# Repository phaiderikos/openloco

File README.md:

> An open source and open hardware DCC decoder for locomotives.

Details.

## Getting started

A quick introduction to get it working.

### PCB

Required PCB capabilities for manifacturing.

### BOM

Table.

### Assembling

Some notes on component placement and soldering.

### Programming

Other notes on SWD.

### Wiring

Table and explanation.

## Features

* Tiny
* Open Hardware and Open Source
* Fully programmable and customizable
* other

## Configuration

Here you should write what are all of the configurations a user can enter when
using the project.

## Contributing

If you'd like to contribute, please fork the repository and use a feature
branch. Pull requests are warmly welcome.

## Links

- Project homepage: none
- Repository: https://github.com/federico1564S/openloco
- Issue tracker: https://github.com/federico1564S/openloco/issues
- Related projects:
  - 1
  - 2

## Licensing

This project is licensed under GPL3 license.

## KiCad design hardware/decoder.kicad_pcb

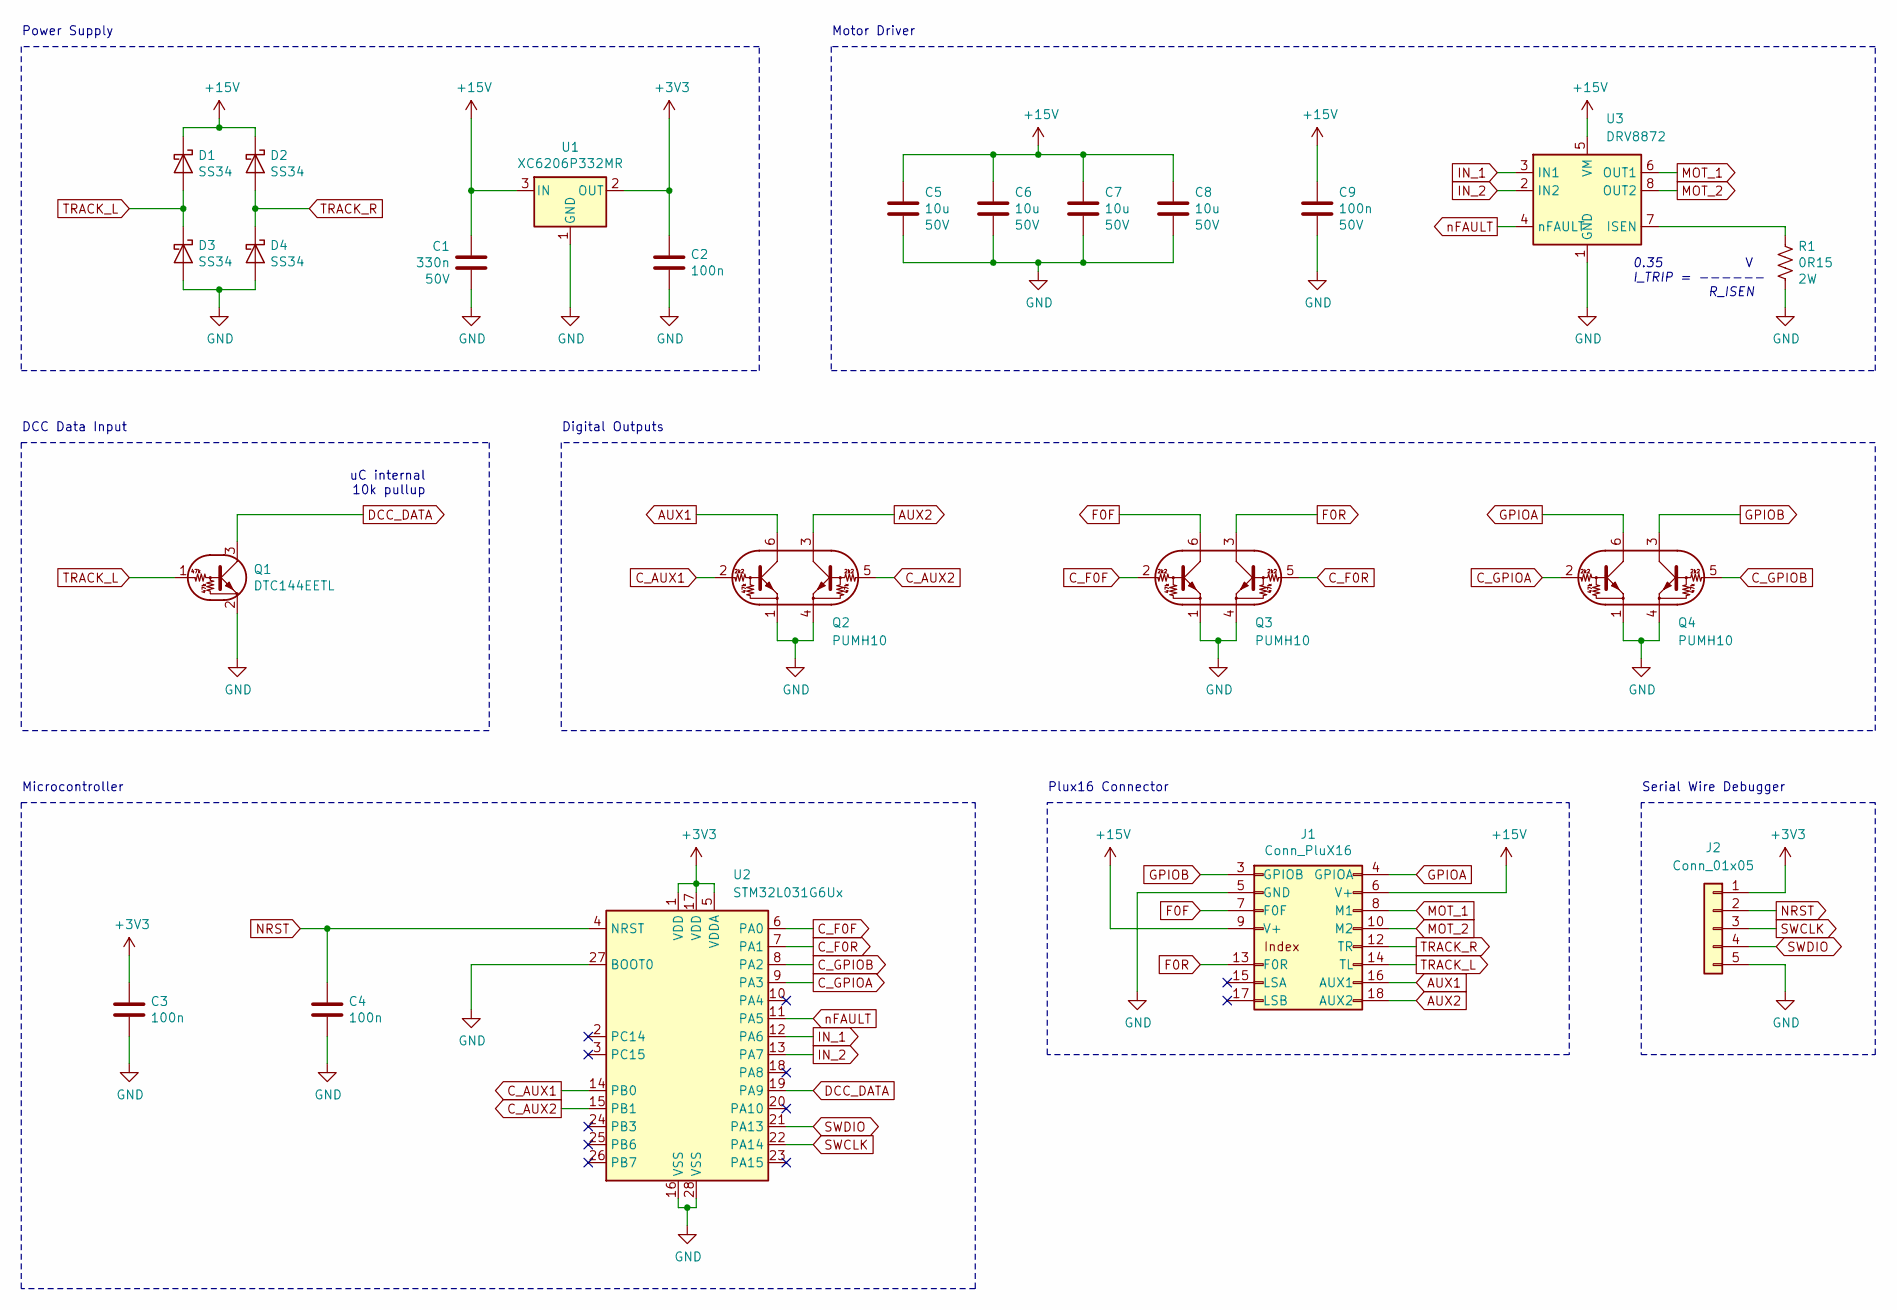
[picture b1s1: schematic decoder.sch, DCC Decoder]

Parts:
C1: 330n; C_1206_3216Metric
C2, C3, C4: 100n; C_0603_1608Metric
C5, C6, C7, C8: 10u; C_1206_3216Metric
C9: 100n; C_0805_2012Metric
D1, D2, D3, D4: SS34; D_SMA
J1: Conn_PluX16; PinHeader_2x08_P1.27mm_Vertical_SMD
J2: Conn_01x05; Pitch_1x05_P1.27mm
Q1: DTC144EETL; SOT-416
Q2, Q3, Q4: PUMH10; SOT-363_SC-70-6
R1: 0R15; R_2512_6332Metric
U1: XC6206P332MR; SOT-23
U2: STM32L031G6Ux; QFN-28_4x4mm_P0.5mm
U3: DRV8872; Texas_HTSOP-8-1EP_3.9x4.9mm_P1.27mm_EP2.95x4.9mm_Mask2.4x3.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

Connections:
+3V3: C2.1, C3.1, J2.1, U1.2 (OUT), U2.1 (VDD), U2.5 (VDDA), U2.17 (VDD)
+15V: C1.1, C5.1, C6.1, C7.1, C8.1, C9.1, D1.1 (K), D2.1 (K), J1.6 (V+), J1.9 (V+), U1.3 (IN), U3.5 (VM)
AUX1: J1.16 (AUX1), Q2.6 (C1)
AUX2: J1.18 (AUX2), Q2.3 (C2)
C_AUX1: Q2.2 (B1), U2.14 (PB0)
C_AUX2: Q2.5 (B2), U2.15 (PB1)
C_F0F: Q3.2 (B1), U2.6 (PA0)
C_F0R: Q3.5 (B2), U2.7 (PA1)
C_GPIOA: Q4.2 (B1), U2.9 (PA3)
C_GPIOB: Q4.5 (B2), U2.8 (PA2)
DCC_DATA: Q1.3 (C), U2.19 (PA9)
F0F: J1.7 (F0F), Q3.6 (C1)
F0R: J1.13 (F0R), Q3.3 (C2)
GND: C1.2, C2.2, C3.2, C4.2, C5.2, C6.2, C7.2, C8.2, C9.2, D3.2 (A), D4.2 (A), J1.5 (GND), J2.5, Q1.2 (E), Q2.1 (E1), Q2.4 (E2), Q3.1 (E1), Q3.4 (E2), Q4.1 (E1), Q4.4 (E2), R1.2, U1.1 (GND), U2.16 (VSS), U2.27 (BOOT0), U2.28 (VSS), U3.1 (GND), U3.9 (GND)
GPIOA: J1.4 (GPIOA), Q4.6 (C1)
GPIOB: J1.3 (GPIOB), Q4.3 (C2)
IN_1: U2.12 (PA6), U3.3 (IN1)
IN_2: U2.13 (PA7), U3.2 (IN2)
MOT_1: J1.8 (M1), U3.6 (OUT1)
MOT_2: J1.10 (M2), U3.8 (OUT2)
NRST: C4.1, J2.2, U2.4 (NRST)
unnamed: R1.1, U3.7 (ISEN)
SWCLK: J2.3, U2.22 (PA14)
SWDIO: J2.4, U2.21 (PA13)
TRACK_L: D1.2 (A), D3.1 (K), J1.14 (TL), Q1.1 (B)
TRACK_R: D2.2 (A), D4.1 (K), J1.12 (TR)
nFAULT: U2.11 (PA5), U3.4 (nFAULT)

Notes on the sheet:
DCC Data Input
Power Supply
uC internal 10k pullup
Serial Wire Debugger
Microcontroller
Motor Driver
Digital Outputs
0.35 I_TRIP = ------ R_ISEN
Plux16 Connector

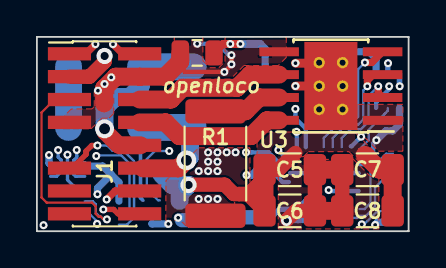
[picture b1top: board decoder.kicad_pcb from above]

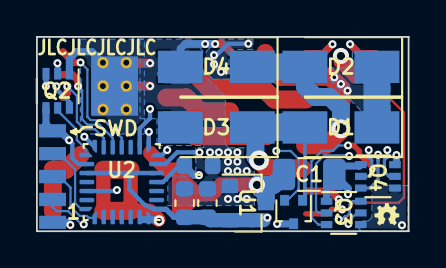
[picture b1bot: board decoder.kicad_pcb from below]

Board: 4 copper layers, 20.7 x 10.8 mm, 23 parts (15 on the bottom side), 27 nets.

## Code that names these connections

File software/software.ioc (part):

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Mcu.Name=STM32L031G(4-6)Ux
Mcu.Package=UFQFPN28
Mcu.UserName=STM32L031G6Ux
PA0-CK_IN.GPIOParameters=GPIO_Label
PA0-CK_IN.GPIO_Label=C_FOF
PA0-CK_IN.Signal=GPIO_Output
PA1.GPIOParameters=GPIO_Label
PA1.GPIO_Label=C_FOR
PA1.Signal=GPIO_Output
PA10.Mode=Asynchronous
PA10.Signal=USART2_RX
PA13.Mode=Serial_Wire
PA13.Signal=SYS_SWDIO
PA14.Mode=Serial_Wire
PA14.Signal=SYS_SWCLK
PA2.GPIOParameters=GPIO_Label
PA2.GPIO_Label=C_GPIOB
PA2.Signal=GPIO_Output
PA3.GPIOParameters=GPIO_Label
PA3.GPIO_Label=C_GPIOA
PA3.Signal=GPIO_Output
PA5.GPIOParameters=GPIO_Label
PA5.GPIO_Label=nFAULT
PA5.Signal=GPIO_Input
PA6.GPIOParameters=GPIO_Speed,GPIO_Label
PA6.GPIO_Label=IN_1
PA6.GPIO_Speed=GPIO_SPEED_FREQ_VERY_HIGH
PA6.Signal=S_TIM22_CH1
PA7.GPIOParameters=GPIO_Speed,GPIO_Label
PA7.GPIO_Label=IN_2
PA7.GPIO_Speed=GPIO_SPEED_FREQ_VERY_HIGH
PA7.Signal=S_TIM22_CH2
PA9.GPIOParameters=GPIO_PuPd,GPIO_Label
PA9.GPIO_Label=DCC_DATA
PA9.GPIO_PuPd=GPIO_PULLUP
PA9.Signal=GPXTI9
PB0.GPIOParameters=GPIO_Label
PB0.GPIO_Label=C_AUX1
PB0.Signal=GPIO_Output
PB1.GPIOParameters=GPIO_Label
PB1.GPIO_Label=C_AUX2
PB1.Signal=GPIO_Output
PB6.Mode=Asynchronous
PB6.Signal=USART2_TX
RCC.HSE_VALUE=8000000
RCC.SYSCLKFreq_VALUE=32000000
RCC.SYSCLKSource=RCC_SYSCLKSOURCE_PLLCLK
board=custom

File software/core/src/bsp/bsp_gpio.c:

/*******************************************************************************
 * @file    :   bsp_gpio.c
 * @brief   :   Board support package for the handling the GPIOs
 * @author  :   Davide Campagna
 * @date    :   May 02, 2024
 * @version :   V1.0
 ******************************************************************************/

/* Includes ----------------------------------------------------------------- */
#include "bsp.h"
#include "qpc.h"

/* Private defines ---------------------------------------------------------- */

Q_DEFINE_THIS_MODULE("BSP_GPIO")

#define FLT_PIN_MASK        ((uint32_t)0xFFu)

/* Front headlight - PluX16 pin 7 */
#define C_FOF_Pin           GPIO_PIN_0
#define C_FOF_GPIO_Port     GPIOA
/* Rear headlight - PluX16 pin 13 */
#define C_FOR_Pin           GPIO_PIN_1
#define C_FOR_GPIO_Port     GPIOA
/* PluX16 pins 3 and 4*/
#define C_GPIOB_Pin         GPIO_PIN_2
#define C_GPIOB_GPIO_Port   GPIOA
#define C_GPIOA_Pin         GPIO_PIN_3
#define C_GPIOA_GPIO_Port   GPIOA
/* DRV8872 control pins */
#define nFAULT_Pin          GPIO_PIN_5
#define nFAULT_GPIO_Port    GPIOA
#define IN_1_Pin            GPIO_PIN_6
#define IN_1_GPIO_Port      GPIOA
#define IN_2_Pin            GPIO_PIN_7
#define IN_2_GPIO_Port      GPIOA
/* PluX16 pins 16 and 18 */
#define C_AUX1_Pin          GPIO_PIN_0
#define C_AUX1_GPIO_Port    GPIOB
#define C_AUX2_Pin          GPIO_PIN_1
#define C_AUX2_GPIO_Port    GPIOB
/* DCC signal coming from the tracks */
#define DCC_DATA_Pin        GPIO_PIN_9
#define DCC_DATA_GPIO_Port  GPIOA

/* Private typedefs --------------------------------------------------------- */
typedef struct {
    GPIO_TypeDef *port;
    GPIO_InitTypeDef cfg;
    void (*isr)(void);
} GPIOPin;

/* Private functions declarations ------------------------------------------- */

static void PluX16_GPIO_Init(void);
static void DCC_GPIO_Init(void);
static void Motor_GPIO_Init(void);

static inline void init_pin(GPIOPin *const pin);
static inline void write_pin(GPIOPin *const pin, GPIO_PinState const state);

/* PluX16 Functions pins ---------------------------------------------------- */
static GPIOPin pin_C_FOF = {
    .port = C_FOF_GPIO_Port,
    .cfg = {
        .Pin = C_FOF_Pin,
        .Mode = GPIO_MODE_OUTPUT_PP,
        .Pull = GPIO_NOPULL,
        .Speed = GPIO_SPEED_FREQ_LOW
    },
    .isr = NULL
};

static GPIOPin pin_C_FOR = {
    .port = C_FOR_GPIO_Port,
    .cfg = {
        .Pin = C_FOR_Pin,
        .Mode = GPIO_MODE_OUTPUT_PP,
        .Pull = GPIO_NOPULL,
        .Speed = GPIO_SPEED_FREQ_LOW
    },
    .isr = NULL
};

static GPIOPin pin_C_GPIOA = {
    .port = C_GPIOA_GPIO_Port,
    .cfg = {
        .Pin = C_GPIOA_Pin,
        .Mode = GPIO_MODE_OUTPUT_PP,
        .Pull = GPIO_NOPULL,
        .Speed = GPIO_SPEED_FREQ_LOW
    },
    .isr = NULL
};

static GPIOPin pin_C_GPIOB = {
    .port = C_GPIOB_GPIO_Port,
    .cfg = {
        .Pin = C_GPIOB_Pin,
        .Pull = GPIO_NOPULL,
#ifdef Q_SPY
        .Mode = GPIO_MODE_AF_PP,
        .Alternate = GPIO_AF4_USART2,
        .Speed = GPIO_SPEED_FREQ_VERY_HIGH,
#else
        .Mode = GPIO_MODE_OUTPUT_PP, .Speed = GPIO_SPEED_FREQ_LOW,
#endif
    },
    .isr = NULL
};

static GPIOPin pin_C_AUX1 = {
    .port = C_AUX1_GPIO_Port,
    .cfg = {
        .Pin = C_AUX1_Pin,
        .Mode = GPIO_MODE_OUTPUT_PP,
        .Pull = GPIO_NOPULL,
        .Speed = GPIO_SPEED_FREQ_LOW
    },
    .isr = NULL
};

static GPIOPin pin_C_AUX2 = {
    .port = C_AUX2_GPIO_Port,
    .cfg = {
        .Pin = C_AUX2_Pin,
        .Mode = GPIO_MODE_OUTPUT_PP,
        .Pull = GPIO_NOPULL,
        .Speed = GPIO_SPEED_FREQ_LOW
    },
    .isr = NULL
};

/* DCC Pins ----------------------------------------------------------------- */
static GPIOPin pin_DCC_DATA = {
    .port = DCC_DATA_GPIO_Port,
    .cfg = {
        .Pin = DCC_DATA_Pin,
        .Mode = GPIO_MODE_IT_RISING_FALLING,
        .Pull = GPIO_PULLUP
    }
};

/* Motor dirver Pins -------------------------------------------------------- */
static GPIOPin pin_nFAULT = {
    .port = nFAULT_GPIO_Port,
    .cfg = {
        .Pin = nFAULT_Pin,
        .Mode = GPIO_MODE_INPUT,
        .Pull = GPIO_PULLUP
    }
};

static GPIOPin pin_IN1 = {
    .port = IN_1_GPIO_Port,
    .cfg = {
        .Pin = IN_1_Pin,
        .Mode = GPIO_MODE_AF_PP,
        .Pull = GPIO_NOPULL,
        .Speed = GPIO_SPEED_FREQ_VERY_HIGH,
        .Alternate = GPIO_AF5_TIM22
    }
};

static GPIOPin pin_IN2 = {
    .port = IN_2_GPIO_Port,
    .cfg = {
        .Pin = IN_2_Pin,
        .Mode = GPIO_MODE_AF_PP,
        .Pull = GPIO_NOPULL,
        .Speed = GPIO_SPEED_FREQ_VERY_HIGH,
        .Alternate = GPIO_AF5_TIM22
    }
};

#ifdef Q_SPY
/* Local QSpy source IDs */
static QSpyId const input_sample = {0};
#endif

/* Private helper functions definitions ------------------------------------- */

static inline void init_pin(GPIOPin *const pin)
{
    /* Pre-conditions */
    Q_REQUIRE(NULL != pin);

    HAL_GPIO_Init(pin->port, &pin->cfg);
}

static inline void write_pin(GPIOPin *const pin, GPIO_PinState const state)
{
    /* Pre-conditions */
    Q_REQUIRE(NULL != pin);

    HAL_GPIO_WritePin(pin->port, pin->cfg.Pin, state);
}

/* Private initialization functions ----------------------------------------- */

static void PluX16_GPIO_Init(void)
{
    /* Init pins */
    init_pin(&pin_C_FOF);
    init_pin(&pin_C_FOR);
    init_pin(&pin_C_GPIOA);
    init_pin(&pin_C_GPIOB);
    init_pin(&pin_C_AUX1);
    init_pin(&pin_C_AUX2);
}

static void DCC_GPIO_Init(void)
{
    init_pin(&pin_DCC_DATA);
}

static void Motor_GPIO_Init(void)
{
    /**
     * TIM22 GPIO Configuration
     * PA6     ------> TIM22_CH1
     * PA7     ------> TIM22_CH2
     */

    init_pin(&pin_nFAULT);
    init_pin(&pin_IN1);
    init_pin(&pin_IN2);
}

/* BSP GPIO Functions ------------------------------------------------------- */

void BSP_InitGPIOs(void)
{
    /* Enable clock for used GPIO Ports */
    __HAL_RCC_GPIOA_CLK_ENABLE();
    __HAL_RCC_GPIOB_CLK_ENABLE();

    PluX16_GPIO_Init();
    DCC_GPIO_Init();
    Motor_GPIO_Init();
}

void BSP_SetCFOF_pin(GPIO_PinState const state)
{
    write_pin(&pin_C_FOF, state);
}

void BSP_SetCFOR_pin(GPIO_PinState const state)
{
    write_pin(&pin_C_FOR, state);
}

void BSP_SetAUX1_pin(GPIO_PinState const state)
{
    write_pin(&pin_C_AUX1, state);
}

void BSP_SetAUX2_pin(GPIO_PinState const state)
{
    write_pin(&pin_C_AUX2, state);
}

void BSP_SetGPIOA_pin(GPIO_PinState const state)
{
    write_pin(&pin_C_GPIOA, state);
}

void BSP_SetGPIOB_pin(GPIO_PinState const state)
{
    write_pin(&pin_C_GPIOB, state);
}

void BSP_RegisterDCCExtIIsr(void (*isr)(void))
{
    pin_DCC_DATA.isr = isr;
}

void BSP_EnableDCCEXTI(void)
{
    HAL_NVIC_EnableIRQ(EXTI4_15_IRQn);
}

void input_sample(void)
{
    static QEvt flt_asserted = QEVT_INITIALIZER(MOTOR_FAULT_ASSERT_SIG);
    static QEvt flt_cleared = QEVT_INITIALIZER(MOTOR_FAULT_CLEAR_SIG);

    static uint32_t flt_mask = 0u;
    static GPIO_PinState last_flt_state = GPIO_PIN_RESET;

    flt_mask <<= 1u;

    if (HAL_GPIO_ReadPin(pin_nFAULT.port, pin_nFAULT.cfg.Pin) == GPIO_PIN_SET) {
        flt_mask |= 1u;
    }

    flt_mask &= (FLT_PIN_MASK);

    /* Handle Fault pin inverted logic */
    if ((flt_mask == 0u) && (last_flt_state = GPIO_PIN_SET)) {
        /* Fault asserted */
        QACTIVE_POST(ao_motor, &flt_asserted, &input_sample);
    } else if ((flt_mask == (FLT_PIN_MASK)) && (last_flt_state = GPIO_PIN_RESET)) {
        /* Fault cleared */
        QACTIVE_POST(ao_motor, &flt_cleared, &input_sample);
    }
}

/* ISR ---------------------------------------------------------------------- */
void HAL_GPIO_EXTI_Callback(uint16_t GPIO_Pin)
{
    if (GPIO_Pin == pin_DCC_DATA.cfg.Pin) {
        if (pin_DCC_DATA.isr != NULL) {
            pin_DCC_DATA.isr();
        }
    }
}

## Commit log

2020-05-28 placeholder readme
2020-06-09 Added .gitignore
2020-06-09 Updated .gitignore
2020-06-09 Added KiCAD project
2020-06-09 Corrected 3V3 pad of µC too big (caused solder bridges with next pad)
2020-06-09 Added logo
2020-06-09 Added logo to README
2022-09-10 Added basic firmware for the µC
2022-09-10 Added basic decoding capabilities and placeholder functions
2022-10-12 [SW] Added initial EEPROM support. Not tested yet.
2024-06-13 [SW] Migration to QuantumFramework as a test.
2025-02-27 Updated and added QP as submodule.
2025-03-03 Added motor control functions.
    Motor control AO was updated to control the DRV via the BSP.
    nFault pin is now sampled at 1ms rate, with a 15ms debounce filter.
    Some code was rearranged to improve code quality.
2025-09-15 Fixed decoder reset behaviour on input timeout.
    Fixed decoder behaviour that would cause the complete loss of all data
    followin a single input timeout, even after another complete and
    correct preamble. The problem was solved by not resetting the timer
    each time a timeout would occur.
    Conected the decoding function to the reception complete event.
    The decoder was tested for the first time with a 12V DCC signal.
